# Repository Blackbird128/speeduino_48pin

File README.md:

# speeduino_48pin
Custom speeduino v0.4.4d hardware made to fit a standard housing with dual 24-pin Delphi connectors.

Simpler and lower cost alternative to the Speeduino Dropbear while keeping the same form factor and full compatibility with the Speeduino v0.4.4d hardware.

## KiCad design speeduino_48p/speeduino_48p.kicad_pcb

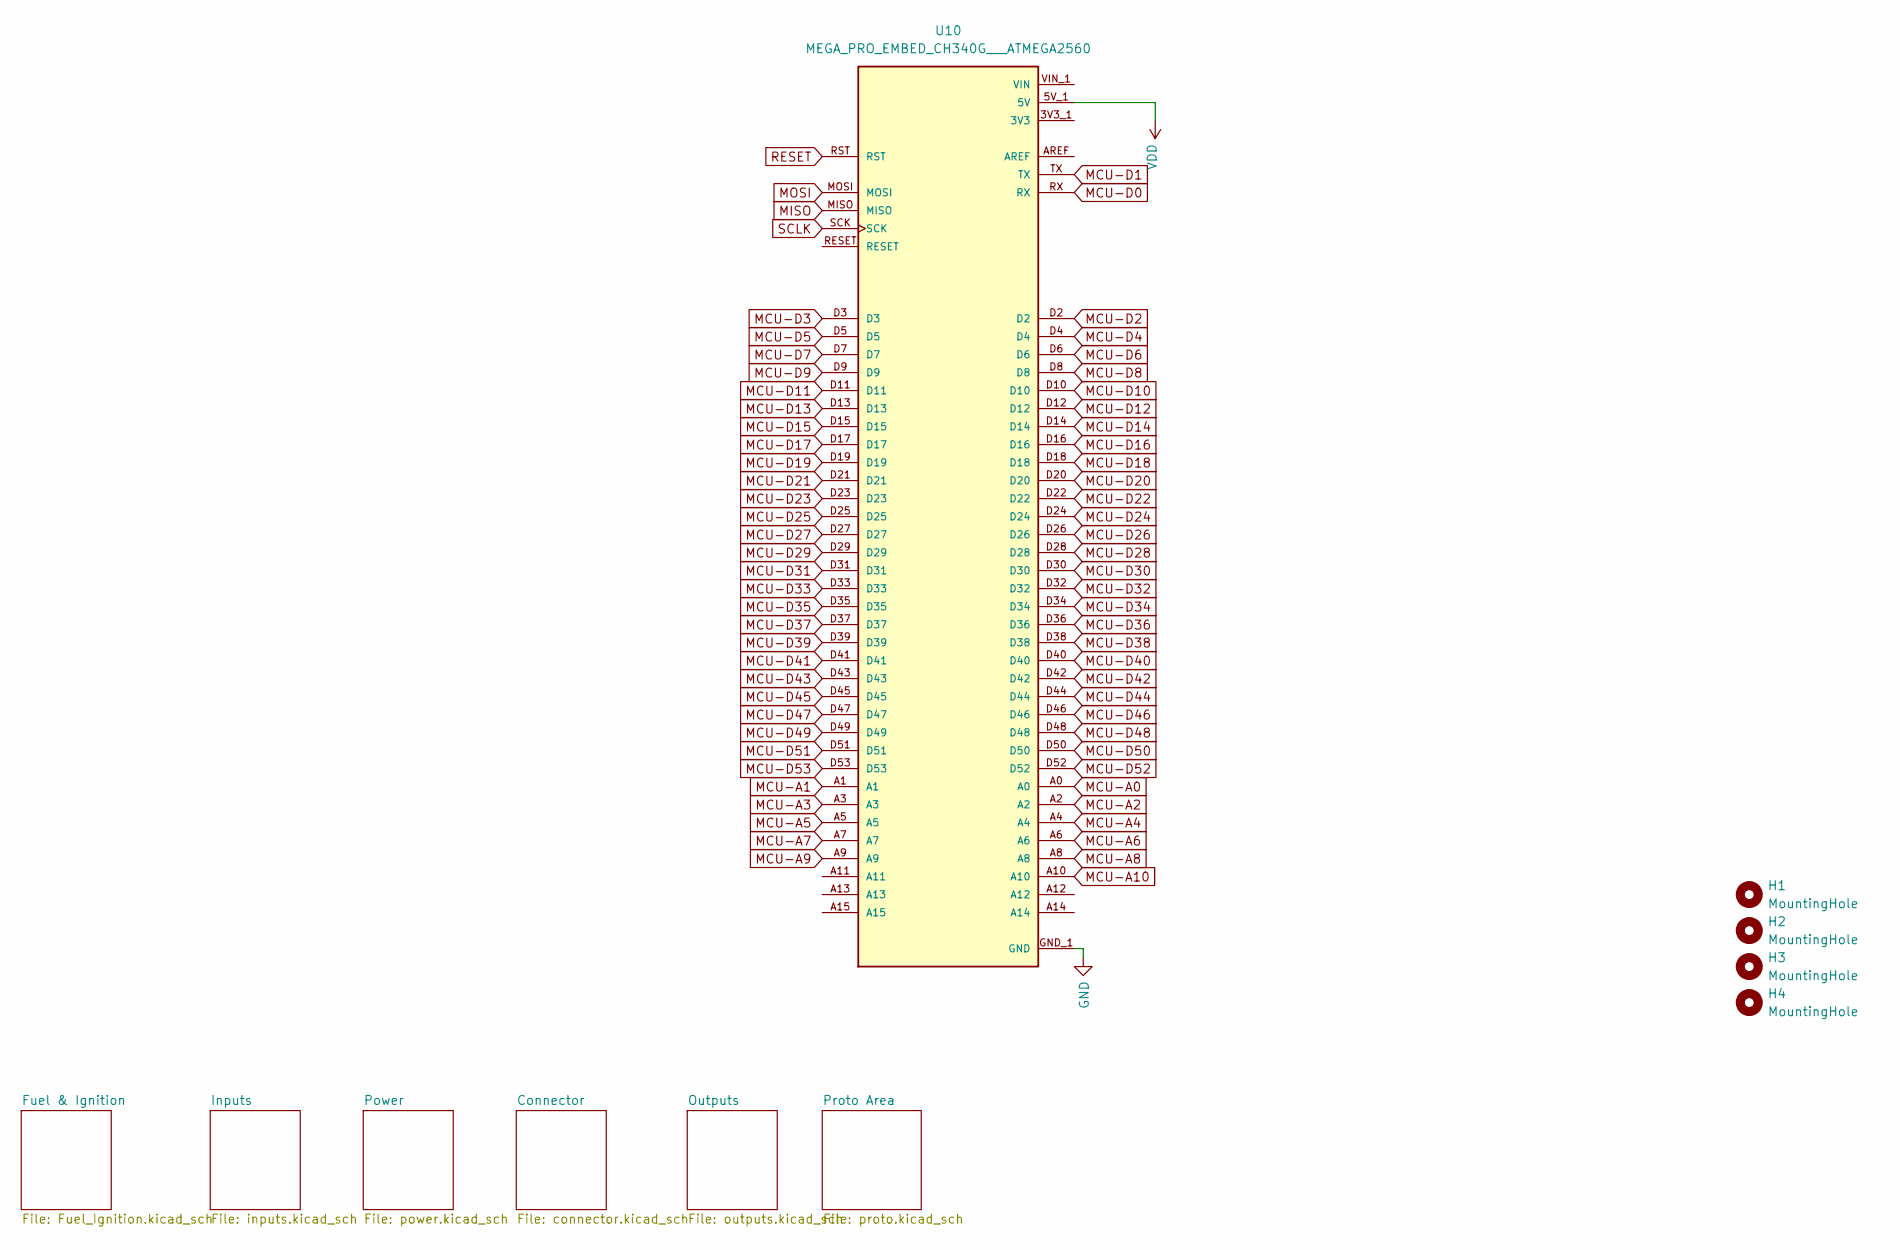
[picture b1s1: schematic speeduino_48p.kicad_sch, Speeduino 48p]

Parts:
H1, H2, H3, H4: MountingHole; MountingHole_3.2mm_M3_DIN965_Pad
U10: MEGA_PRO_EMBED_CH340G___ATMEGA2560; 2560ProMini; PARTREV 12/May/2017

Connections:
3V3: U10.3V3_1 (3V3), U10.3V3_2 (3V3)
ADC-Clamp-1: U10.A4; also elsewhere on the board
ADC-Clamp-2: U10.A3; also elsewhere on the board
ADC-Clamp-3: U10.A1; also elsewhere on the board
ADC-Clamp-4: U10.A2; also elsewhere on the board
ADC-Clamp-5: U10.A0; also elsewhere on the board
ADC-Clamp-6: U10.A8; also elsewhere on the board
ADC-Clamp-8: U10.D18; also elsewhere on the board
ADC-Clamp-9: U10.D19; also elsewhere on the board
ADC-Clamp-10: U10.D2; also elsewhere on the board
ADC-Clamp-13: U10.D51; also elsewhere on the board
GND: U10.GND_1 (GND), U10.GND_2 (GND), U10.GND_3 (GND); also elsewhere on the board
MCU-A5: U10.A5; also elsewhere on the board
MCU-A6: U10.A6
MCU-A7: U10.A7
MCU-A9: U10.A9; also elsewhere on the board
MCU-A10: U10.A10; also elsewhere on the board
MCU-D0: U10.RX; also elsewhere on the board
MCU-D1: U10.TX; also elsewhere on the board
MCU-D3: U10.D3; also elsewhere on the board
MCU-D4: U10.D4; also elsewhere on the board
MCU-D5: U10.D5; also elsewhere on the board
MCU-D6: U10.D6; also elsewhere on the board
MCU-D7: U10.D7; also elsewhere on the board
MCU-D8: U10.D8; also elsewhere on the board
MCU-D9: U10.D9; also elsewhere on the board
MCU-D10: U10.D10; also elsewhere on the board
MCU-D11: U10.D11; also elsewhere on the board
MCU-D12: U10.D12
MCU-D13: U10.D13
MCU-D14: U10.D14; also elsewhere on the board
MCU-D15: U10.D15; also elsewhere on the board
MCU-D16: U10.D16; also elsewhere on the board
MCU-D17: U10.D17; also elsewhere on the board
MCU-D20: U10.D20; also elsewhere on the board
MCU-D21: U10.D21; also elsewhere on the board
MCU-D22: U10.D22
MCU-D23: U10.D23
MCU-D24: U10.D24; also elsewhere on the board
MCU-D25: U10.D25
MCU-D26: U10.D26
MCU-D27: U10.D27
MCU-D28: U10.D28
MCU-D29: U10.D29
MCU-D30: U10.D30
MCU-D31: U10.D31
MCU-D32: U10.D32
MCU-D33: U10.D33
MCU-D34: U10.D34
MCU-D35: U10.D35
MCU-D36: U10.D36
MCU-D37: U10.D37
MCU-D38: U10.D38; also elsewhere on the board
MCU-D39: U10.D39
MCU-D40: U10.D40; also elsewhere on the board
MCU-D41: U10.D41
MCU-D42: U10.D42
MCU-D43: U10.D43
MCU-D44: U10.D44
MCU-D45: U10.D45; also elsewhere on the board
MCU-D46: U10.D46
MCU-D47: U10.D47; also elsewhere on the board
MCU-D48: U10.D48
MCU-D49: U10.D49; also elsewhere on the board
MCU-D50: U10.D50; also elsewhere on the board
MCU-D52: U10.D52; also elsewhere on the board
MCU-D53: U10.D53
MISO: U10.MISO
MOSI: U10.MOSI
RESET: U10.RST; also elsewhere on the board
SCLK: U10.SCK
VDD: U10.5V_1 (5V), U10.5V_2 (5V), U10.5V_3 (5V); also elsewhere on the board
VIN: U10.VIN_1 (VIN), U10.VIN_2 (VIN)

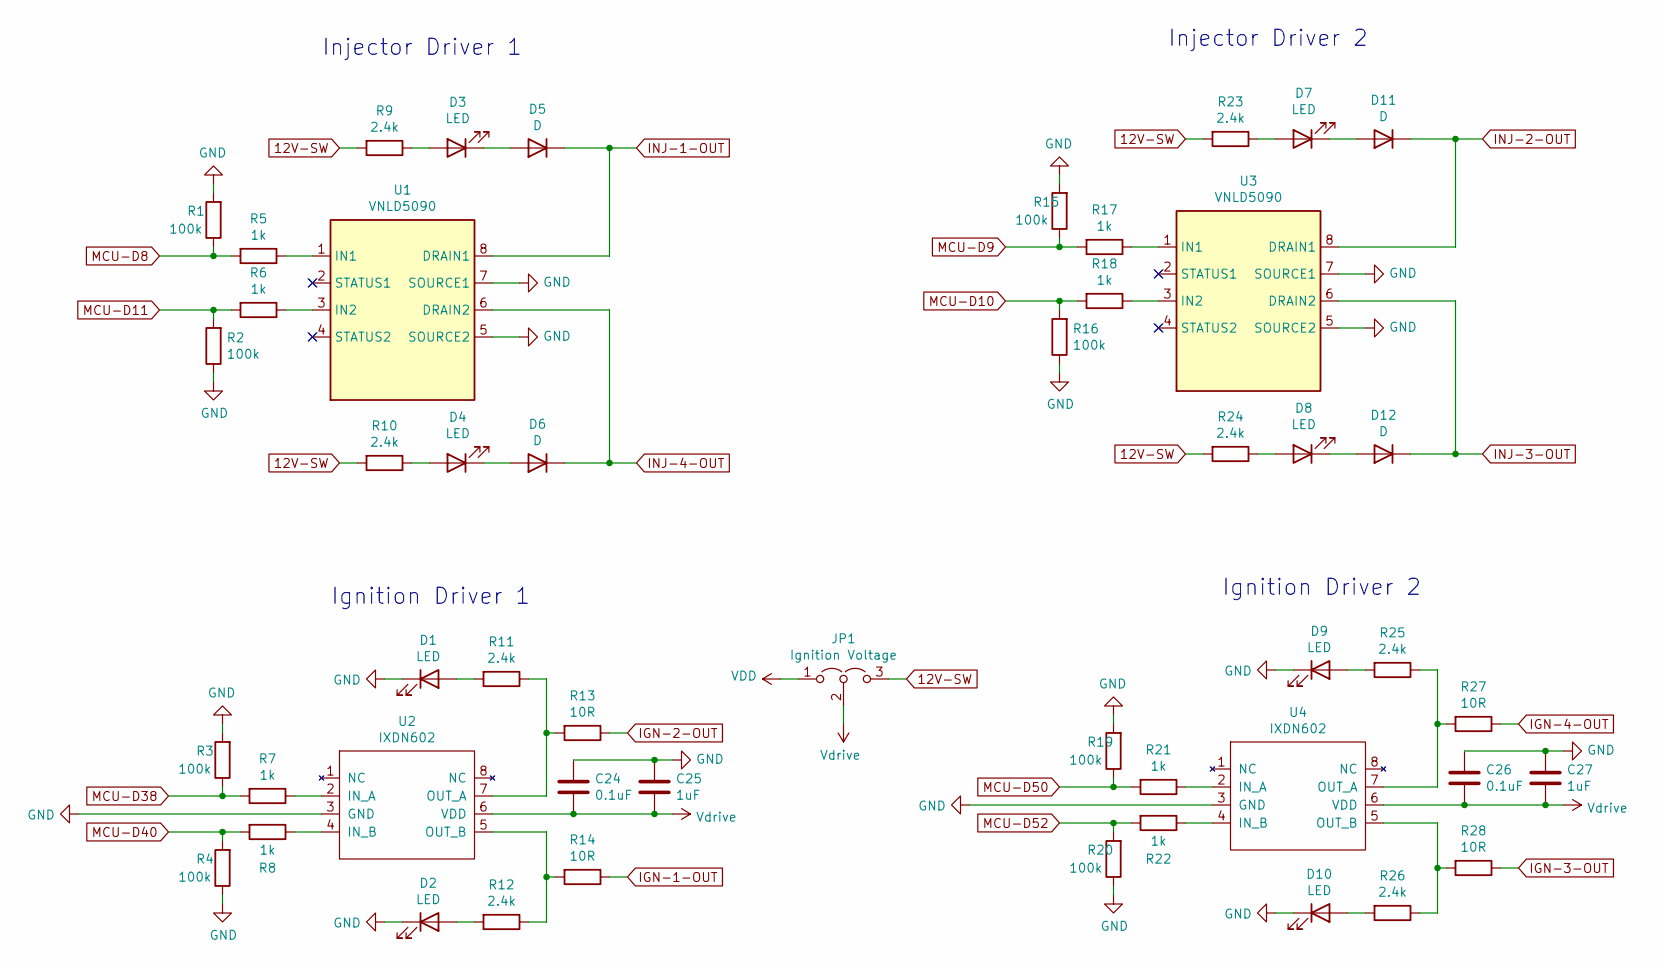
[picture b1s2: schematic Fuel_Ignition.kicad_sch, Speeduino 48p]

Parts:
C24, C26: 0.1uF; C_0805_2012Metric; Manufacturer_Part_Number CC0805KRX7R9BB104; Digikey Part Number 311-1140-1-ND
C25, C27: 1uF; C_0805_2012Metric; Manufacturer_Part_Number CC0805KKX7R7BB105; Digikey Part Number 311-1365-1-ND
D1, D2, D3, D4, D7, D8, D9, D10: LED; LED_0805_2012Metric; Manufacturer_Part_Number LH R974-LP-1; Digikey Part Number 475-1415-1-ND
D5, D6, D11, D12: D; D_SOD-323; Manufacturer_Part_Number 1N4448WX-TP; Digikey Part Number 1N4448WXTPMSCT-ND
JP1: Ignition Voltage; PinHeader_1x03_P2.54mm_Vertical; Manufacturer_Part_Number M20-9990345; Digikey Part Number 952-2263-ND
R1, R2, R3, R4, R15, R16, R19, R20: 100k; R_0805_2012Metric; Manufacturer_Part_Number RC0805FR-07100KL; Digikey Part Number 311-100KCRCT-ND
R5, R6, R7, R8, R17, R18, R21, R22: 1k; R_0805_2012Metric; Manufacturer_Part_Number RC0805FR-071KL; Digikey Part Number 311-1.00KCRCT-ND
R9, R10, R11, R12, R23, R24, R25, R26: 2.4k; R_0805_2012Metric; Manufacturer_Part_Number RC0805FR-072K4L; Digikey Part Number 311-2.40KCRCT-ND
R13, R14, R27, R28: 10R; R_1206_3216Metric; Manufacturer_Part_Number RC1206FR-0710RL; Digikey Part Number 311-10.0FRCT-ND
U1, U3: VNLD5090; SOIC-8_3.9x4.9mm_P1.27mm; Manufacturer_Part_Number VNLD5090-E; Digikey Part Number 497-18682-ND
U2, U4: IXDN602; SOIC-8_3.9x4.9mm_P1.27mm; Manufacturer_Part_Number IXDN602SIATR; Digikey Part Number 212-IXDN602SIACT-ND

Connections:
12V-SW: JP1.3 (B), R9.2, R10.2, R23.2, R24.2; also elsewhere on the board
GND: C24.1, C25.1, C26.1, C27.1, D1.1 (K), D2.1 (K), D9.1 (K), D10.1 (K), R1.2, R2.1, R3.2, R4.1, R15.2, R16.1, R19.2, R20.1, U1.5 (SOURCE2), U1.7 (SOURCE1), U2.3 (GND), U3.5 (SOURCE2), U3.7 (SOURCE1), U4.3 (GND); also elsewhere on the board
IGN-1-OUT: R14.1; also elsewhere on the board
IGN-2-OUT: R13.1; also elsewhere on the board
IGN-3-OUT: R28.1; also elsewhere on the board
IGN-4-OUT: R27.1; also elsewhere on the board
INJ-1-OUT: D5.1 (K), U1.8 (DRAIN1); also elsewhere on the board
INJ-2-OUT: D11.1 (K), U3.8 (DRAIN1); also elsewhere on the board
INJ-3-OUT: D12.1 (K), U3.6 (DRAIN2); also elsewhere on the board
INJ-4-OUT: D6.1 (K), U1.6 (DRAIN2); also elsewhere on the board
MCU-D8: R1.1, R5.2; also elsewhere on the board
MCU-D9: R15.1, R17.2; also elsewhere on the board
MCU-D10: R16.2, R18.2; also elsewhere on the board
MCU-D11: R2.2, R6.2; also elsewhere on the board
MCU-D38: R3.1, R7.2; also elsewhere on the board
MCU-D40: R4.2, R8.2; also elsewhere on the board
MCU-D50: R19.1, R21.2; also elsewhere on the board
MCU-D52: R20.2, R22.2; also elsewhere on the board
unnamed: D1.2 (A), R11.2
unnamed: D2.2 (A), R12.2
unnamed: D3.2 (A), R9.1
unnamed: D3.1 (K), D5.2 (A)
unnamed: D4.2 (A), R10.1
unnamed: D4.1 (K), D6.2 (A)
unnamed: D7.2 (A), R23.1
unnamed: D8.2 (A), R24.1
unnamed: D9.2 (A), R25.2
unnamed: D10.2 (A), R26.2
unnamed: D7.1 (K), D11.2 (A)
unnamed: D8.1 (K), D12.2 (A)
unnamed: R5.1, U1.1 (IN1)
unnamed: R6.1, U1.3 (IN2)
unnamed: R7.1, U2.2 (IN_A)
unnamed: R8.1, U2.4 (IN_B)
unnamed: R11.1, R13.2, U2.7 (OUT_A)
unnamed: R12.1, R14.2, U2.5 (OUT_B)
unnamed: R17.1, U3.1 (IN1)
unnamed: R18.1, U3.3 (IN2)
unnamed: R21.1, U4.2 (IN_A)
unnamed: R22.1, U4.4 (IN_B)
unnamed: R25.1, R27.2, U4.7 (OUT_A)
unnamed: R26.1, R28.2, U4.5 (OUT_B)
VDD: JP1.1 (A); also elsewhere on the board
Vdrive: C24.2, C25.2, C26.2, C27.2, JP1.2 (C), U2.6 (VDD), U4.6 (VDD)

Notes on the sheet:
Ignition Driver 2
Injector Driver 2
Injector Driver 1
Ignition Driver 1

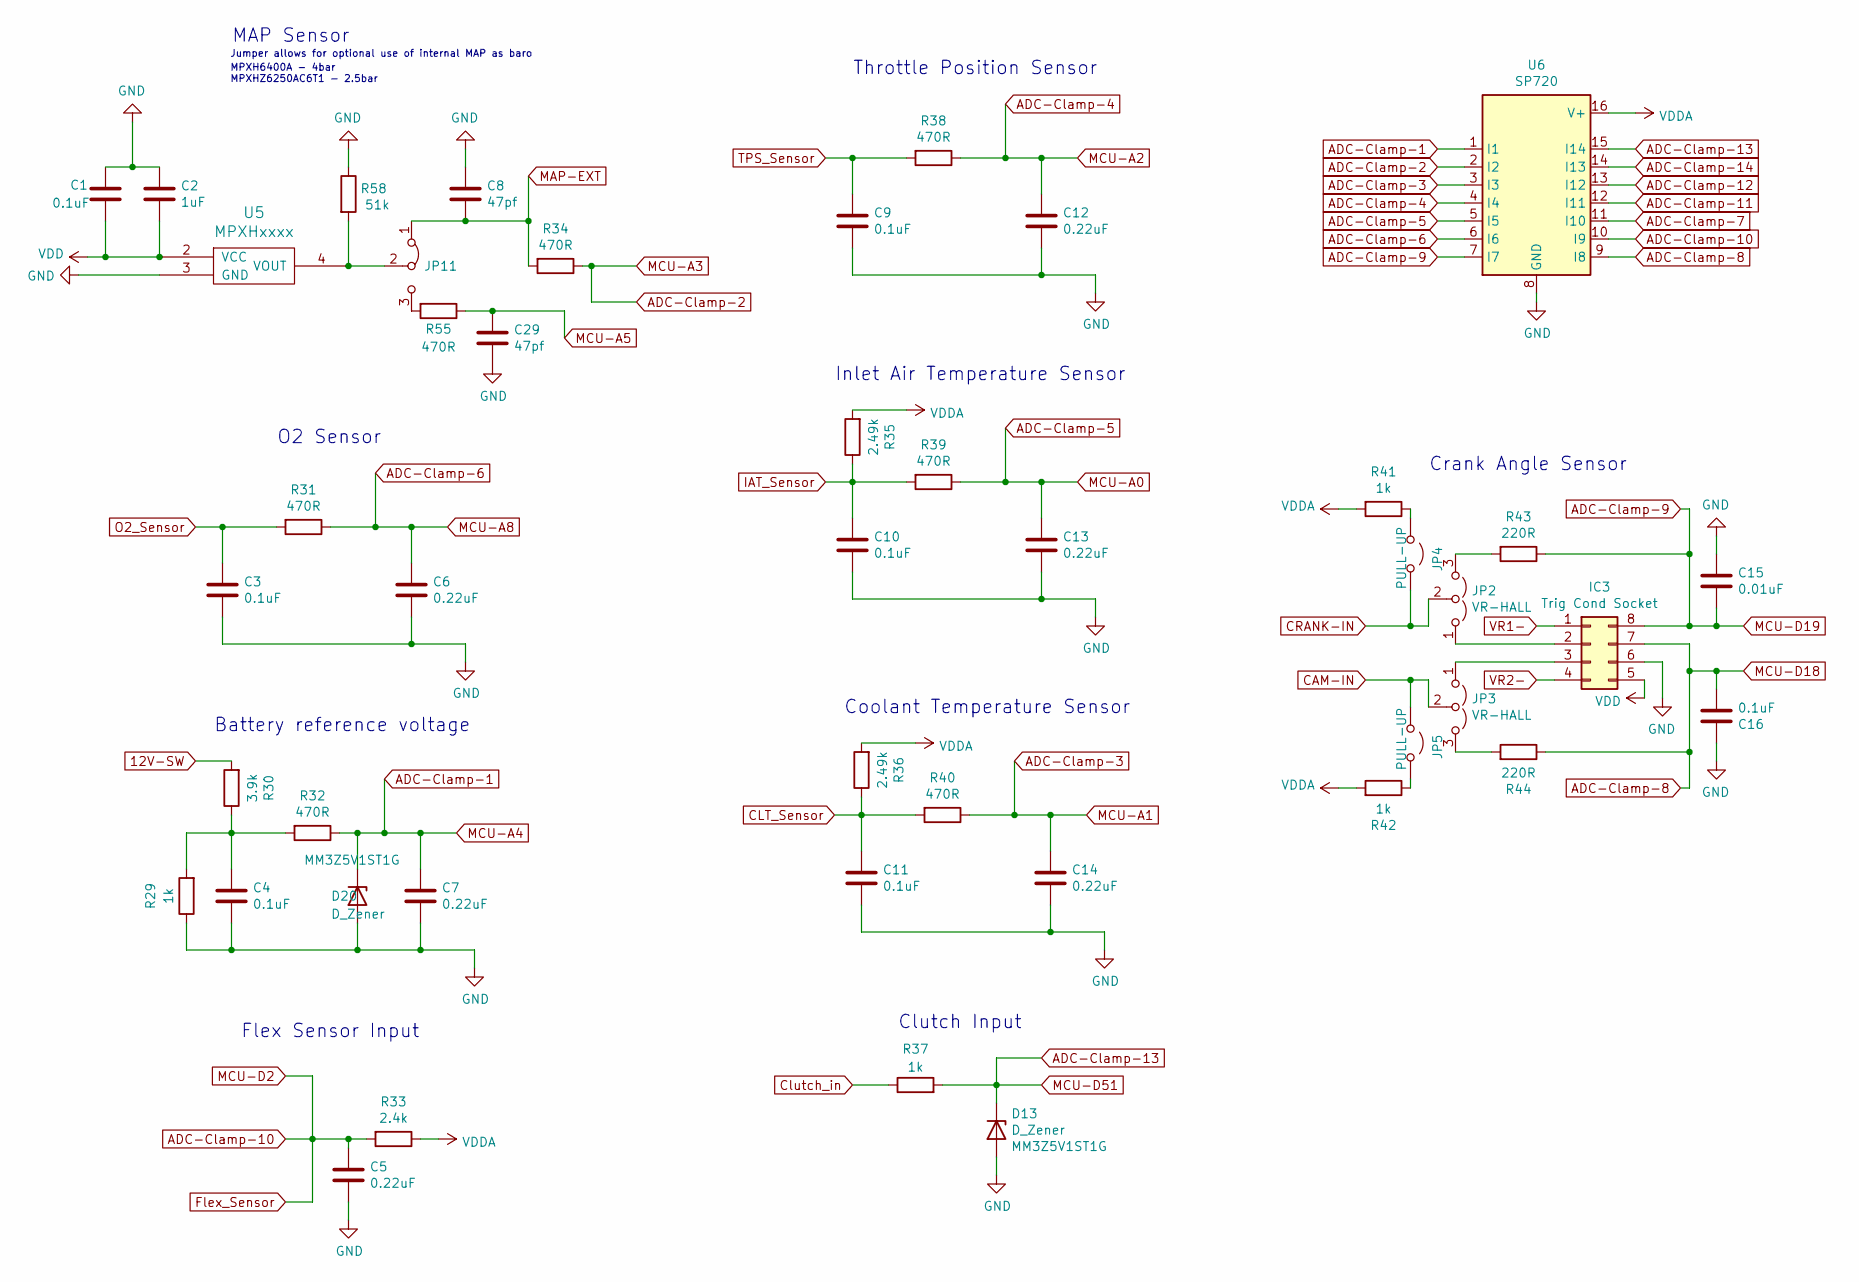
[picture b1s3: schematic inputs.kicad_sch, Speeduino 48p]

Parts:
C1: 0.1uF; C_0805_2012Metric; Manufacturer_Part_Number CC0805KRX7R9BB103; Digikey Part Number 311-1136-1-ND
C2: 1uF; C_0805_2012Metric; Manufacturer_Part_Number CC0805KKX7R7BB105; Digikey Part Number 311-1365-1-ND
C3, C4, C9, C10, C11, C16: 0.1uF; C_0805_2012Metric; Manufacturer_Part_Number CC0805KRX7R9BB104; Digikey Part Number 311-1140-1-ND
C5, C6, C7, C12, C13, C14: 0.22uF; C_0805_2012Metric; Manufacturer_Part_Number CL21B224KOCNNNC; Digikey Part Number 1276-1284-1-ND
C8, C29: 47pf; C_0805_2012Metric; Manufacturer_Part_Number CC0805KRX7R9BB471; Digikey Part Number 311-1124-1-ND
C15: 0.01uF; C_0805_2012Metric; Manufacturer_Part_Number CC0805KRX7R9BB103; Digikey Part Number 311-1136-1-ND
D13, D20: D_Zener; D_SOD-323; Part # MM3Z5V1ST1G; Digikey Part Number MM3Z5V1ST1GOSCT-ND
IC3: Trig Cond Socket; DIP-8_W7.62mm_Socket
JP2, JP3: VR-HALL; PinHeader_1x03_P2.54mm_Vertical; Manufacturer_Part_Number M20-9990345; Digikey Part Number 952-2263-ND
JP4, JP5: PULL-UP; PinHeader_1x02_P2.54mm_Vertical; Manufacturer_Part_Number M20-9990245; Digikey Part Number 952-2261-ND
JP11: Jumper_3_Bridged12; SolderJumper-3_P1.3mm_Bridged12_RoundedPad1.0x1.5mm
R29, R37, R41, R42: 1k; R_0805_2012Metric; Manufacturer_Part_Number RC0805FR-071KL; Digikey Part Number 311-1.00KCRCT-ND
R30: 3.9k; R_0805_2012Metric; Manufacturer_Part_Number RC0805FR-073K9L; Digikey Part Number 311-3.90KCRCT-ND
R31, R32, R34, R38, R39, R40, R55: 470R; R_0805_2012Metric; Manufacturer_Part_Number ERJ-6ENF4700V; Digikey Part Number P470CCT-ND
R33: 2.4k; R_0805_2012Metric; Manufacturer_Part_Number RC0805FR-072K4L; Digikey Part Number 311-2.40KCRCT-ND
R35, R36: 2.49k; R_0805_2012Metric; Manufacturer_Part_Number RT0805BRD072K49L; Digikey Part Number YAG1854CT-ND
R43, R44: 220R; R_0805_2012Metric; Manufacturer_Part_Number RC0805FR-07220RL; Digikey Part Number 311-220CRCT-ND
R58: 51k; R_0805_2012Metric; Manufacturer_Part_Number ERJ-6ENF4700V; Digikey Part Number P470CCT-ND
U5: MPXHxxxx; SOP-8_3.76x4.96mm_P1.27mm; Manufacturer_Part_Number MPXH6400A; Digikey Part Number MPXH6400A
U6: SP720; SOIC-16_3.9x9.9mm_P1.27mm; Manufacturer_Part_Number SP720ABTG; Digikey Part Number F3162CT-ND

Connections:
12V-SW: R30.2; also elsewhere on the board
ADC-Clamp-1: C7.1, D20.1 (K), R32.1, U6.1 (I1); also elsewhere on the board
ADC-Clamp-2: R34.1, U6.2 (I2); also elsewhere on the board
ADC-Clamp-3: C14.1, R40.1, U6.3 (I3); also elsewhere on the board
ADC-Clamp-4: C12.1, R38.1, U6.4 (I4); also elsewhere on the board
ADC-Clamp-5: C13.1, R39.1, U6.5 (I5); also elsewhere on the board
ADC-Clamp-6: C6.1, R31.1, U6.6 (I6); also elsewhere on the board
ADC-Clamp-7: U6.11 (I10)
ADC-Clamp-8: C16.2, IC3.7, R44.1, U6.9 (I8); also elsewhere on the board
ADC-Clamp-9: C15.2, IC3.8, R43.1, U6.7 (I7); also elsewhere on the board
ADC-Clamp-10: C5.1, R33.2, U6.10 (I9); also elsewhere on the board
ADC-Clamp-11: U6.12 (I11)
ADC-Clamp-12: U6.13 (I12)
ADC-Clamp-13: D13.1 (K), R37.2, U6.15 (I14); also elsewhere on the board
ADC-Clamp-14: U6.14 (I13)
CAM-IN: JP3.2 (C), JP5.1 (A); also elsewhere on the board
CLT_Sensor: C11.1, R36.1, R40.2; also elsewhere on the board
CRANK-IN: JP2.2 (C), JP4.1 (A); also elsewhere on the board
Clutch_in: R37.1; also elsewhere on the board
GND: C1.1, C2.1, C3.2, C4.2, C5.2, C6.2, C7.2, C8.1, C9.2, C10.2, C11.2, C12.2, C13.2, C14.2, C15.1, C16.1, C29.2, D13.2 (A), D20.2 (A), IC3.6, R29.1, R58.1, U5.3 (GND), U6.8 (GND); also elsewhere on the board
IAT_Sensor: C10.1, R35.1, R39.2; also elsewhere on the board
MAP-EXT: C8.2, JP11.1 (A), R34.2; also elsewhere on the board
MCU-A5: C29.1, R55.1; also elsewhere on the board
unnamed: C4.1, R29.2, R30.1, R32.2
unnamed: IC3.2, JP2.1 (A)
unnamed: IC3.3, JP3.1 (A)
unnamed: JP2.3 (B), R43.2
unnamed: JP3.3 (B), R44.2
unnamed: JP4.2 (B), R41.1
unnamed: JP5.2 (B), R42.1
unnamed: JP11.3 (B), R55.2
unnamed: JP11.2 (C), R58.2, U5.4 (VOUT)
O2_Sensor: C3.1, R31.2; also elsewhere on the board
TPS_Sensor: C9.1, R38.2; also elsewhere on the board
VDD: C1.2, C2.2, IC3.5, U5.2 (VCC); also elsewhere on the board
VDDA: R33.1, R35.2, R36.2, R41.2, R42.2, U6.16 (V+); also elsewhere on the board
VR1-: IC3.1; also elsewhere on the board
VR2-: IC3.4; also elsewhere on the board

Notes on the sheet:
Clutch Input
MPXH6400A - 4bar MPXHZ6250AC6T1 - 2.5bar
O2 Sensor
Coolant Temperature Sensor
Inlet Air Temperature Sensor
MAP Sensor
Battery reference voltage
Crank Angle Sensor
Throttle Position Sensor
Flex Sensor Input
Jumper allows for optional use of internal MAP as baro

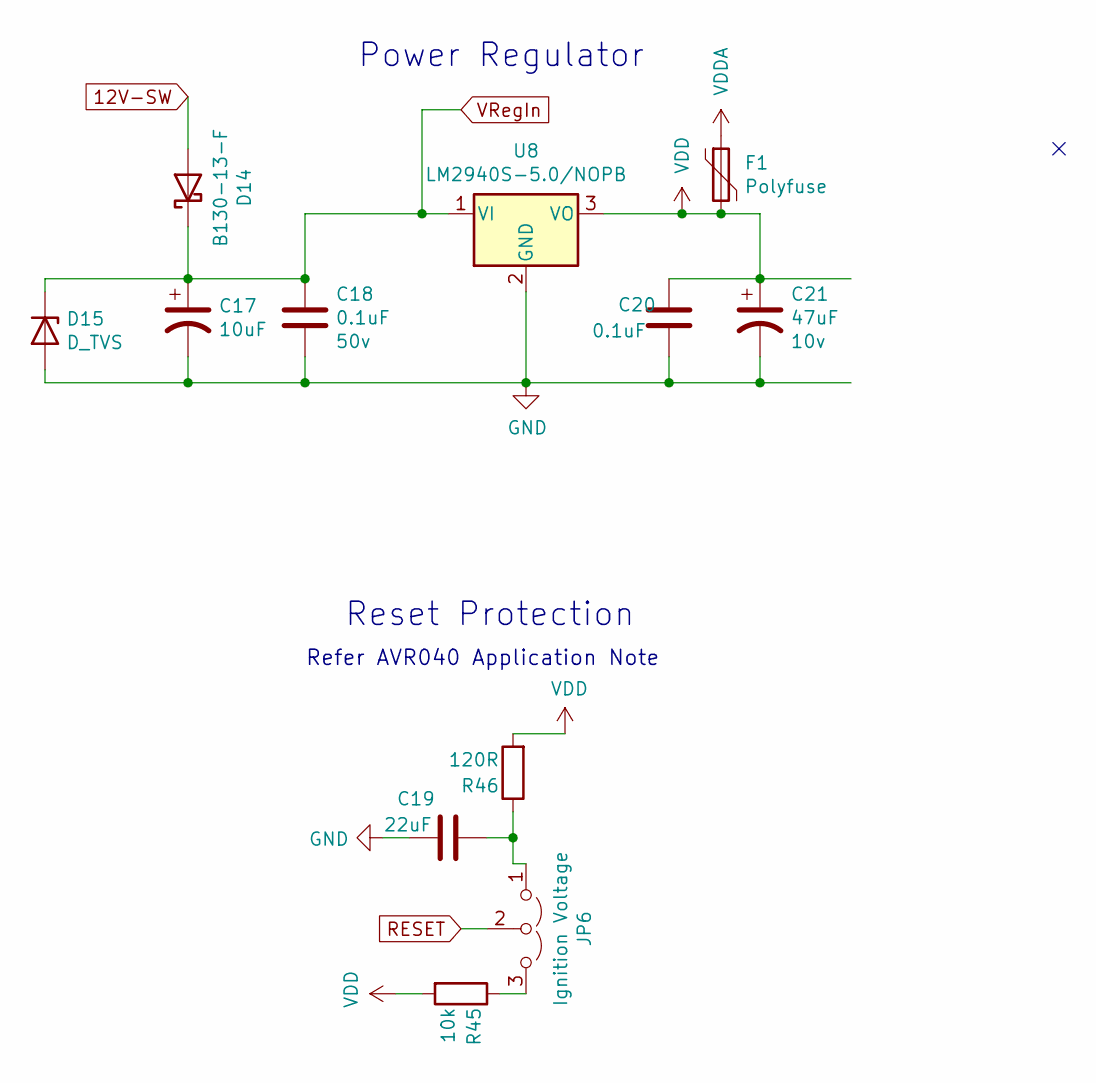
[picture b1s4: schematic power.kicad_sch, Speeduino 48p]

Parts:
C17: 10uF; CP_EIA-7343-31_Kemet-D; Voltage 35v; Manufacturer_Part_Number T491D106K050AT; Digikey Part Number 399-8361-1-ND
C18: 0.1uF; C_0805_2012Metric; Voltage 50v; Manufacturer_Part_Number CC0805KRX7R9BB104; Digikey Part Number 311-1140-1-ND
C19: 22uF; C_0805_2012Metric_Pad1.18x1.45mm_HandSolder; Manufacturer_Part_Number CL21A226KQCLRNC; Digikey Part Number 1276-6687-1-ND
C20: 0.1uF; C_0805_2012Metric; Manufacturer_Part_Number CC0805KRX7R9BB104; Digikey Part Number 311-1140-1-ND
C21: 47uF; CP_EIA-3528-21_Kemet-B; Voltage 10v; Manufacturer_Part_Number TAJB476K006RNJ; Digikey Part Number 478-1692-1-ND
D14: B130-13-F; D_SMA; Manufacturer_Part_Number B130-13-F; Digikey Part Number B130-FDICT-ND
D15: D_TVS; D_SMB; Manufacturer_Part_Number SMBJ40A-Q; Digikey Part Number SMBJ40A-QCT-ND
F1: Polyfuse; Fuse_1812_4532Metric; Manufacturer_Part_Number 0ZCC0050FF2C; Digikey Part Number 507-1361-1-ND
JP6: Ignition Voltage; PinHeader_1x03_P2.54mm_Vertical; Manufacturer_Part_Number M20-9990345; Digikey Part Number 952-2263-ND
R45: 10k; R_0805_2012Metric; Manufacturer_Part_Number RC0805JR-0710KL; Digikey Part Number 311-10KARCT-ND
R46: 120R; R_0805_2012Metric; Manufacturer_Part_Number RC0805FR-07120RL; Digikey Part Number 311-120CRCT-ND
U8: LM2940S-5.0/NOPB; TO-263-3_TabPin2; Manufacturer_Part_Number LM2940S-5.0/NOPB; Digikey Part Number LM2940S-5.0/NOPB-ND

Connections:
12V-SW: D14.2 (A); also elsewhere on the board
GND: C17.2, C18.2, C19.2, C20.2, C21.2, D15.2 (A), U8.2 (GND); also elsewhere on the board
unnamed: C19.1, JP6.1 (A), R46.1
unnamed: JP6.3 (B), R45.1
RESET: JP6.2 (C); also elsewhere on the board
VDD: C20.1, C21.1, F1.2, R45.2, R46.2, U8.3 (VO); also elsewhere on the board
VDDA: F1.1; also elsewhere on the board
VRegIn: C17.1, C18.1, D14.1 (K), D15.1 (K), U8.1 (VI)

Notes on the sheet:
Reset Protection
Power Regulator
Refer AVR040 Application Note

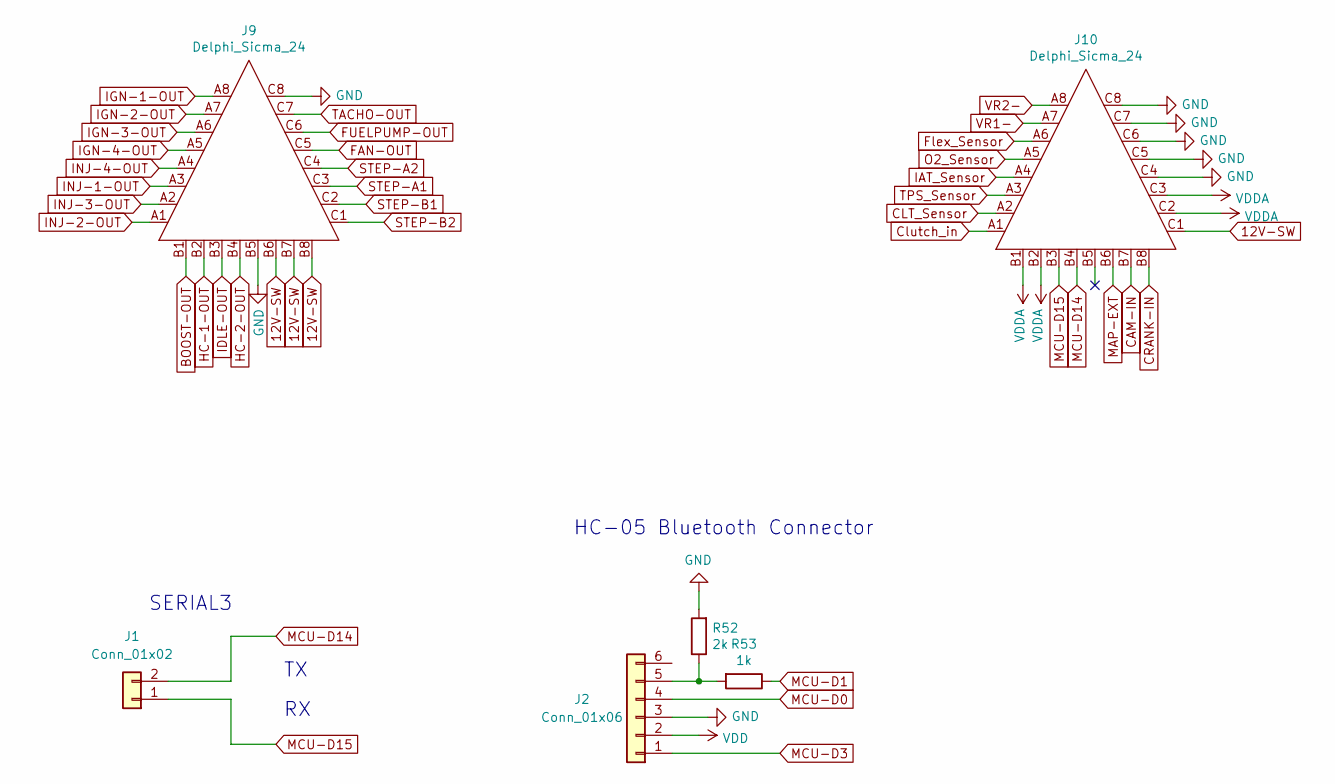
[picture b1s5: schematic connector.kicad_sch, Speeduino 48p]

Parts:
J1: Conn_01x02; PinHeader_1x02_P2.54mm_Vertical
J2: Conn_01x06; PinHeader_1x06_P2.54mm_Vertical
J9: Delphi_Sicma_24; Delphi_Sicma_24_Grey
J10: Delphi_Sicma_24; Delphi_Sicma_24_Black
R52: 2k; R_0805_2012Metric; Manufacturer_Part_Number RC0805FR-072KL; Digikey Part Number 311-2.00KCRCT-ND
R53: 1k; R_0805_2012Metric; Manufacturer_Part_Number RC0805FR-071KL; Digikey Part Number 311-1.00KCRCT-ND

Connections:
12V-SW: J9.B6, J9.B7, J9.B8, J10.C1; also elsewhere on the board
ADC-Clamp-10: J10.A6; also elsewhere on the board
BOOST-OUT: J9.B1; also elsewhere on the board
CAM-IN: J10.B7; also elsewhere on the board
CLT_Sensor: J10.A2; also elsewhere on the board
CRANK-IN: J10.B8; also elsewhere on the board
Clutch_in: J10.A1; also elsewhere on the board
FAN-OUT: J9.C5; also elsewhere on the board
FUELPUMP-OUT: J9.C6; also elsewhere on the board
GND: J2.3, J9.B5, J9.C8, J10.C4, J10.C5, J10.C6, J10.C7, J10.C8, R52.2; also elsewhere on the board
HC-1-OUT: J9.B2; also elsewhere on the board
HC-2-OUT: J9.B4; also elsewhere on the board
IAT_Sensor: J10.A4; also elsewhere on the board
IDLE-OUT: J9.B3; also elsewhere on the board
IGN-1-OUT: J9.A8; also elsewhere on the board
IGN-2-OUT: J9.A7; also elsewhere on the board
IGN-3-OUT: J9.A6; also elsewhere on the board
IGN-4-OUT: J9.A5; also elsewhere on the board
INJ-1-OUT: J9.A3; also elsewhere on the board
INJ-2-OUT: J9.A1; also elsewhere on the board
INJ-3-OUT: J9.A2; also elsewhere on the board
INJ-4-OUT: J9.A4; also elsewhere on the board
MAP-EXT: J10.B6; also elsewhere on the board
MCU-D0: J2.4; also elsewhere on the board
MCU-D1: R53.1; also elsewhere on the board
MCU-D3: J2.1; also elsewhere on the board
MCU-D14: J1.2, J10.B4; also elsewhere on the board
MCU-D15: J1.1, J10.B3; also elsewhere on the board
unnamed: J2.5, R52.1, R53.2
O2_Sensor: J10.A5; also elsewhere on the board
STEP-A1: J9.C3; also elsewhere on the board
STEP-A2: J9.C4; also elsewhere on the board
STEP-B1: J9.C2; also elsewhere on the board
STEP-B2: J9.C1; also elsewhere on the board
TACHO-OUT: J9.C7; also elsewhere on the board
TPS_Sensor: J10.A3; also elsewhere on the board
VDD: J2.2; also elsewhere on the board
VDDA: J10.B1, J10.B2, J10.C2, J10.C3; also elsewhere on the board
VR1-: J10.A7; also elsewhere on the board
VR2-: J10.A8; also elsewhere on the board

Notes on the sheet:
SERIAL3
HC-05 Bluetooth Connector

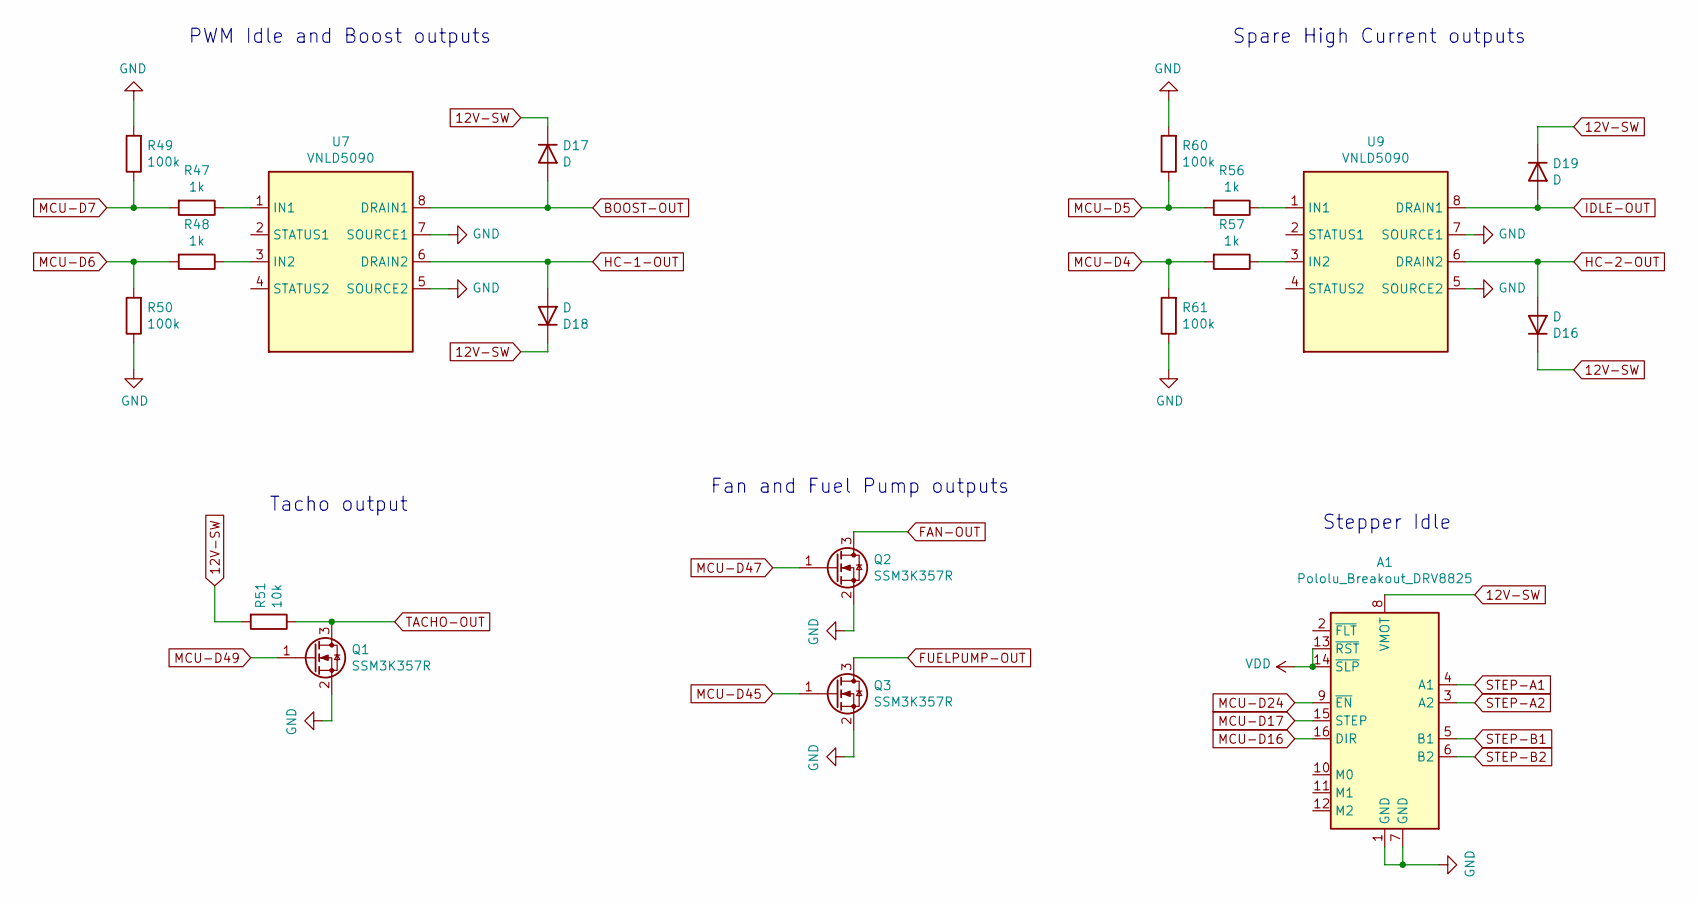
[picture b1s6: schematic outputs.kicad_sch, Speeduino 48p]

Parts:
A1: Pololu_Breakout_DRV8825; Pololu_Breakout-16_15.2x20.3mm
D16, D17, D18, D19: D; D_SOD-123F; Manufacturer_Part_Number S110FA; Digikey Part Number S110FACT-ND
Q1, Q2, Q3: SSM3K357R; SOT-23; Manufacturer_Part_Number SSM3K357R; Digikey Part Number SSM3K357RLFCT-ND
R47, R48, R56, R57: 1k; R_0805_2012Metric; Manufacturer_Part_Number RC0805FR-071KL; Digikey Part Number 311-1.00KCRCT-ND
R49, R50, R60, R61: 100k; R_0805_2012Metric; Manufacturer_Part_Number RC0805FR-07100KL; Digikey Part Number 311-100KCRCT-ND
R51: 10k; R_0805_2012Metric; Manufacturer_Part_Number RC0805JR-0710KL; Digikey Part Number 311-10KARCT-ND
U7, U9: VNLD5090; SOIC-8_3.9x4.9mm_P1.27mm; Manufacturer_Part_Number VNLD5090-E; Digikey Part Number 497-18682-ND

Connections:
12V-SW: A1.8 (VMOT), D16.1 (K), D17.1 (K), D18.1 (K), D19.1 (K), R51.2; also elsewhere on the board
BOOST-OUT: D17.2 (A), U7.8 (DRAIN1); also elsewhere on the board
FAN-OUT: Q2.3 (D); also elsewhere on the board
FUELPUMP-OUT: Q3.3 (D); also elsewhere on the board
GND: A1.1 (GND), A1.7 (GND), Q1.2 (S), Q2.2 (S), Q3.2 (S), R49.2, R50.1, R60.2, R61.1, U7.5 (SOURCE2), U7.7 (SOURCE1), U9.5 (SOURCE2), U9.7 (SOURCE1); also elsewhere on the board
HC-1-OUT: D18.2 (A), U7.6 (DRAIN2); also elsewhere on the board
HC-2-OUT: D16.2 (A), U9.6 (DRAIN2); also elsewhere on the board
IDLE-OUT: D19.2 (A), U9.8 (DRAIN1); also elsewhere on the board
MCU-D4: R57.2, R61.2; also elsewhere on the board
MCU-D5: R56.2, R60.1; also elsewhere on the board
MCU-D6: R48.2, R50.2; also elsewhere on the board
MCU-D7: R47.2, R49.1; also elsewhere on the board
MCU-D16: A1.16 (DIR); also elsewhere on the board
MCU-D17: A1.15 (STEP); also elsewhere on the board
MCU-D24: A1.9 (~EN); also elsewhere on the board
MCU-D45: Q3.1 (G); also elsewhere on the board
MCU-D47: Q2.1 (G); also elsewhere on the board
MCU-D49: Q1.1 (G); also elsewhere on the board
unnamed: R47.1, U7.1 (IN1)
unnamed: R48.1, U7.3 (IN2)
unnamed: R56.1, U9.1 (IN1)
unnamed: R57.1, U9.3 (IN2)
STEP-A1: A1.4 (A1); also elsewhere on the board
STEP-A2: A1.3 (A2); also elsewhere on the board
STEP-B1: A1.5 (B1); also elsewhere on the board
STEP-B2: A1.6 (B2); also elsewhere on the board
TACHO-OUT: Q1.3 (D), R51.1; also elsewhere on the board
VDD: A1.13 (~RST), A1.14 (~SLP); also elsewhere on the board

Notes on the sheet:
Spare High Current outputs
Stepper Idle
PWM Idle and Boost outputs
Fan and Fuel Pump outputs
Tacho output

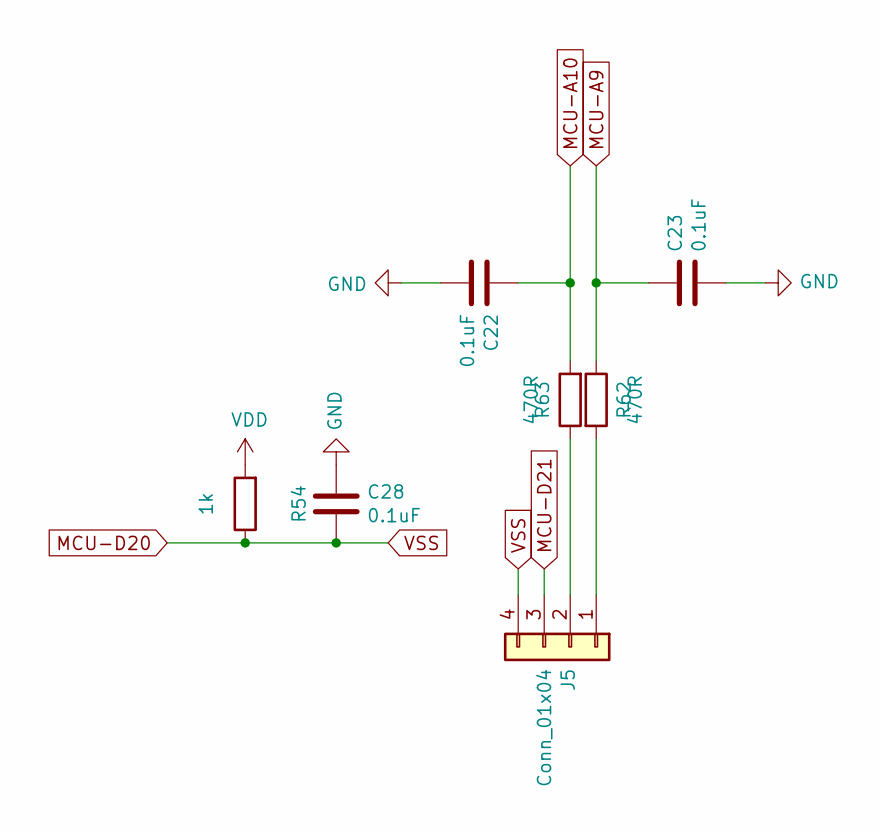
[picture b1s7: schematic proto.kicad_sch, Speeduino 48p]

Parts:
C22, C23, C28: 0.1uF; C_0805_2012Metric; Manufacturer_Part_Number CC0805KRX7R9BB104; Digikey Part Number 311-1140-1-ND
J5: Conn_01x04; PinHeader_1x04_P2.54mm_Vertical
R54: 1k; R_0805_2012Metric; Manufacturer_Part_Number RC0805FR-071KL; Digikey Part Number 311-1.00KCRCT-ND
R62, R63: 470R; R_0805_2012Metric; Manufacturer_Part_Number ERJ-6ENF4700V; Digikey Part Number P470CCT-ND

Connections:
GND: C22.2, C23.2, C28.1; also elsewhere on the board
MCU-A9: C23.1, R63.1; also elsewhere on the board
MCU-A10: C22.1, R62.2; also elsewhere on the board
MCU-D20: C28.2, J5.4, R54.1; also elsewhere on the board
MCU-D21: J5.3; also elsewhere on the board
unnamed: J5.1, R63.2
unnamed: J5.2, R62.1
VDD: R54.2; also elsewhere on the board
